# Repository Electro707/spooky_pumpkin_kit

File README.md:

# Scary Pumpkin Soldering Kit with Touch
## Designed by Electro707

This soldering kit is for a pumpkin in which you can touch the nose area to change the LED's effects,
or put the pumpkin in sleep mode until the next Halloween season!

## Credit
The outline for the board, as mention in the [Outline_Graphics](Outline_Graphics) folder, are a combination of some vector graphics from Wikimedia, which are
- [Pumpkinn.svg](https://commons.wikimedia.org/wiki/File:Pumpkinn.svg), under the [CC0 1.0 Universal Public Domain Dedication](https://creativecommons.org/publicdomain/zero/1.0/deed.en) license.
- [Scary_pumpkin_3.svg](https://commons.wikimedia.org/wiki/File:Scary_pumpkin_3.svg), under the [GNU Free Documentation License](https://commons.wikimedia.org/wiki/Commons:GNU_Free_Documentation_License,_version_1.2)

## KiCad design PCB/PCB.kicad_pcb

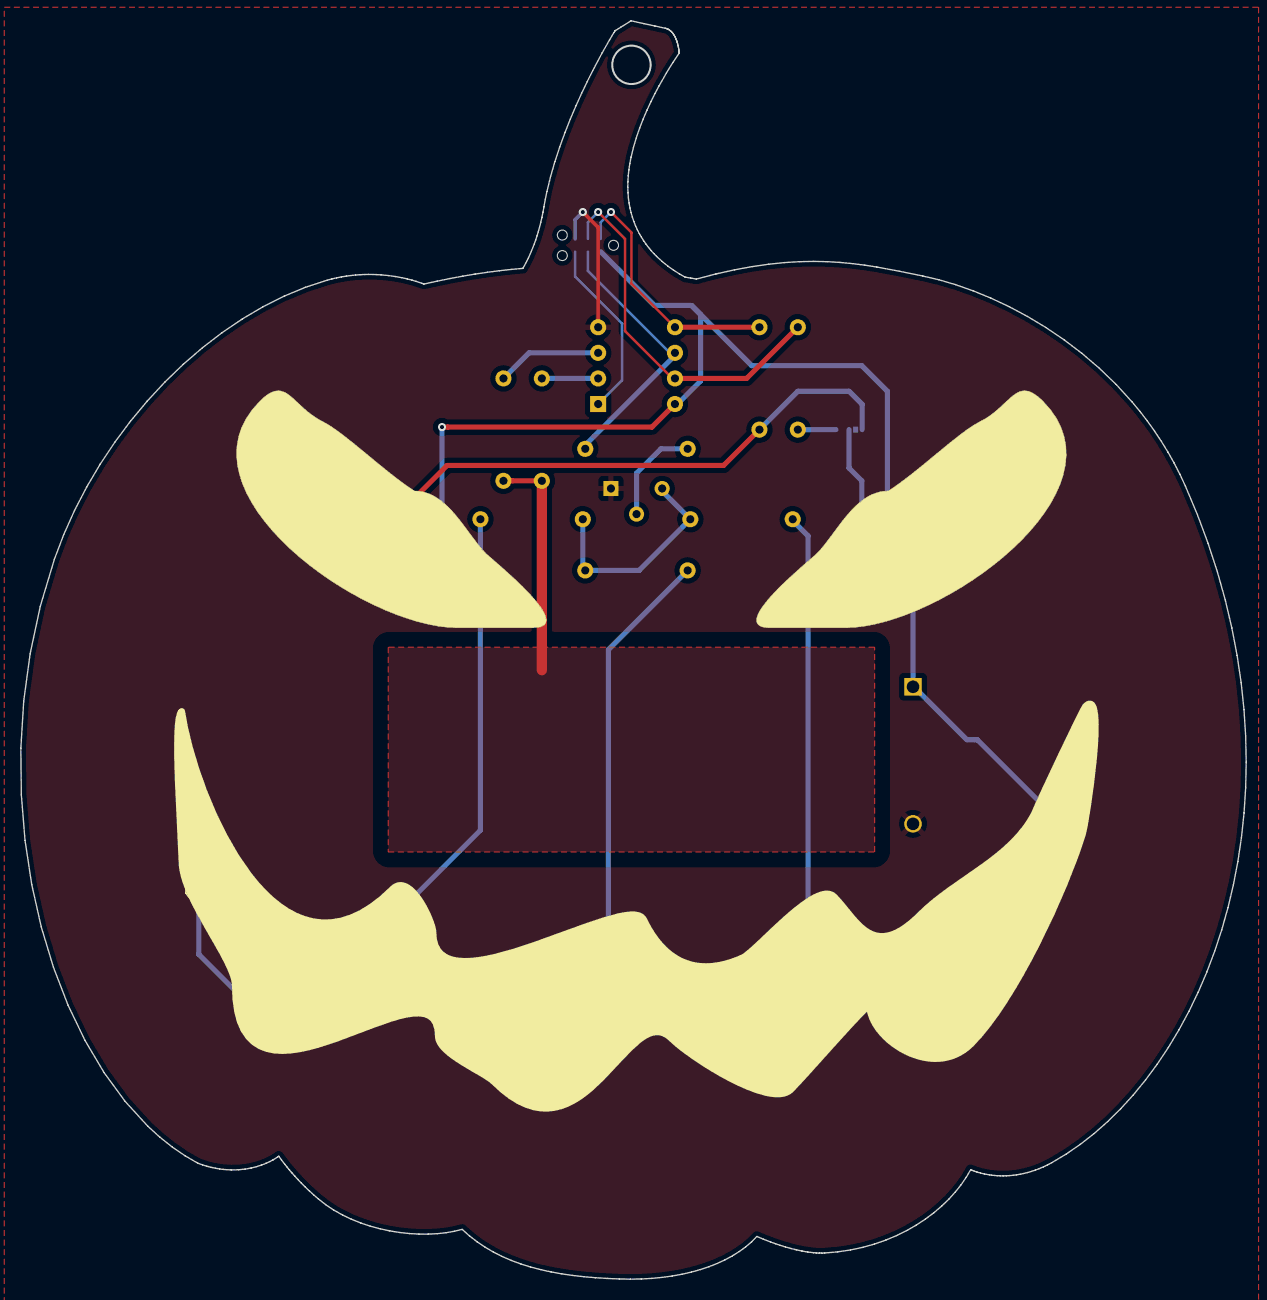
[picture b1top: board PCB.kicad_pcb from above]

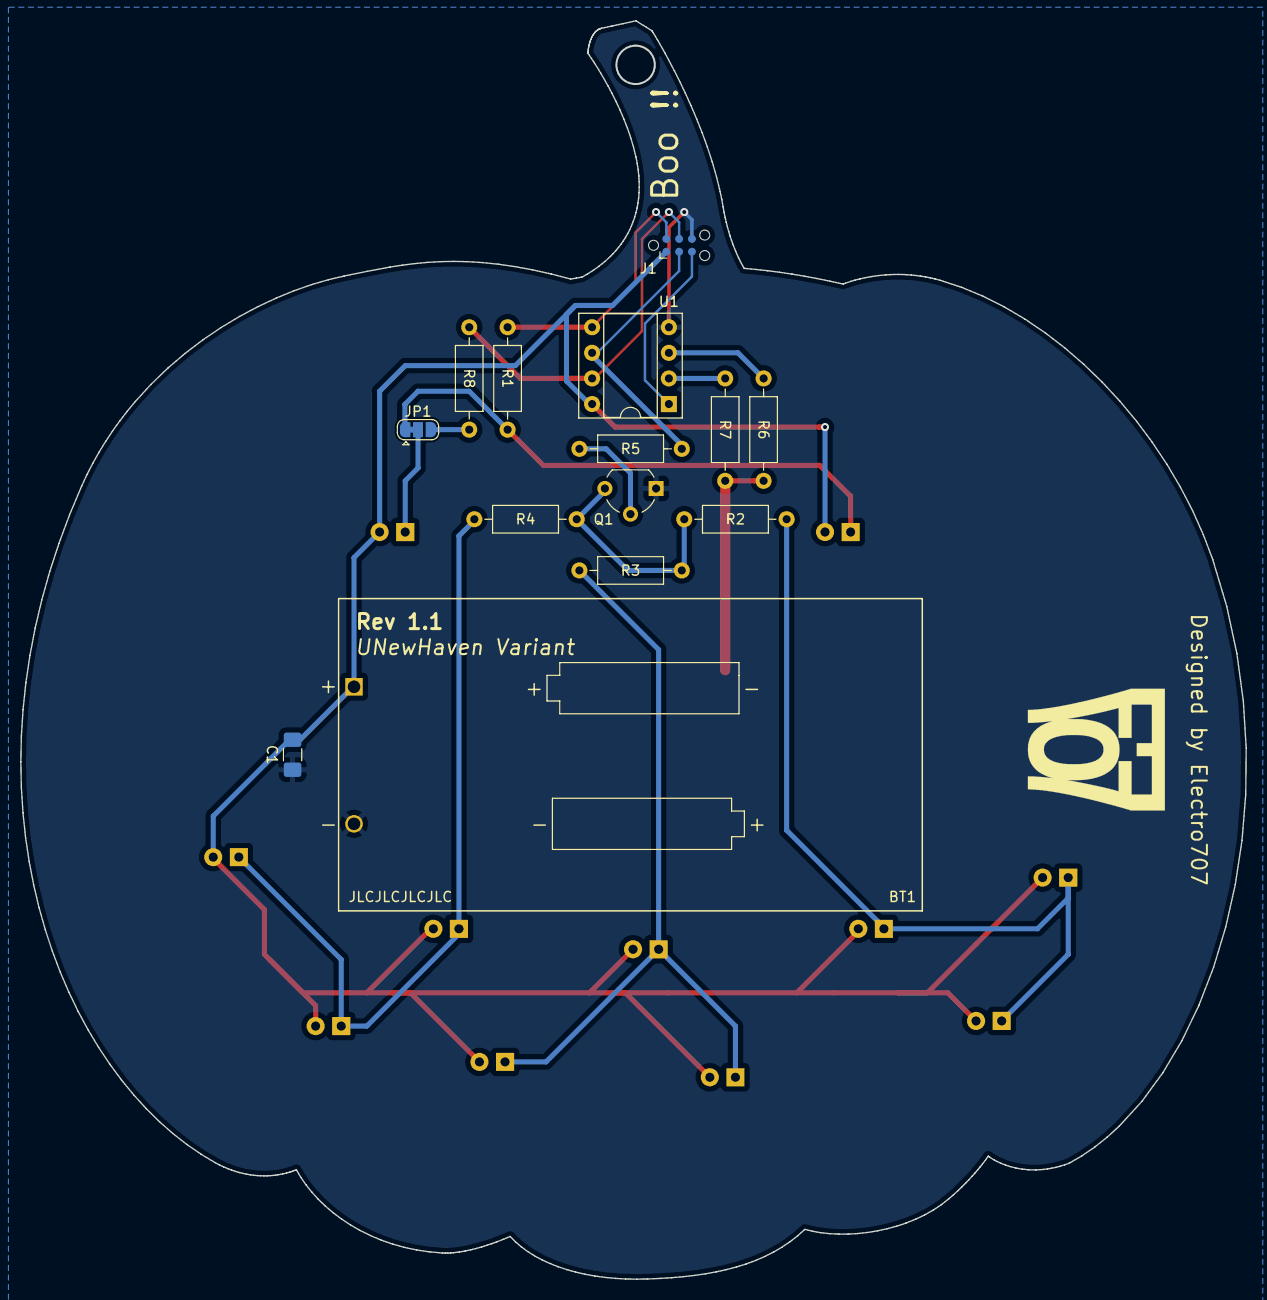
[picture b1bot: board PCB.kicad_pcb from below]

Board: 2 copper layers, 121.6 x 124.9 mm, 25 parts (14 on the bottom side), 17 nets.

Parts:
BT1: Battery; BC2AAPC
C1: 1uF; C_1206_3216Metric_Pad1.42x1.75mm_HandSolder
D1, D2, D3, D4, D5, D6, D7, D8, D9, D10, D11: LED_ALT; LED_D5.0mm
J1: Conn_01x06; Tag-Connect_TC2030-IDC-NL_2x03_P1.27mm_Vertical
JP1: SolderJumper_3_Bridged12; SolderJumper-3_P1.3mm_Bridged12_RoundedPad1.0x1.5mm
Q1: 2N3904; TO-92_Wide
R1, R2, R3, R4, R8: 330; R_Axial_DIN0207_L6.3mm_D2.5mm_P10.16mm_Horizontal
R5, R7: 1k; R_Axial_DIN0207_L6.3mm_D2.5mm_P10.16mm_Horizontal
R6: 1M; R_Axial_DIN0207_L6.3mm_D2.5mm_P10.16mm_Horizontal
U1: ATtiny85-20PU; DIP-8_W7.62mm_Socket

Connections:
CopperPad: R6.2, R7.2
GND: BT1.2 (-), C1.2, J1.6, Q1.1 (E), U1.4 (GND)
unnamed: D1.1 (K), JP1.1 (A), R1.1
unnamed: D2.1 (K), JP1.2 (C)
unnamed: D3.1 (K), D4.1 (K), D5.1 (K), R2.1
unnamed: J1.2, R1.2, U1.5 (AREF/PB0)
unnamed: J1.3, R5.2, U1.6 (PB1)
unnamed: J1.4, R8.2, U1.7 (PB2)
unnamed: J1.5, U1.1 (~RESET/PB5)
unnamed: JP1.3 (B), R8.1
unnamed: Q1.2 (B), R5.1
unnamed: Q1.3 (C), R2.2, R3.2, R4.2
unnamed: D6.1 (K), D7.1 (K), D8.1 (K), R3.1
unnamed: D9.1 (K), D10.1 (K), D11.1 (K), R4.1
unnamed: R7.1, U1.2 (XTAL1/PB3)
unnamed: R6.1, U1.3 (XTAL2/PB4)
VCC: BT1.1 (+), C1.1, D1.2 (A), D2.2 (A), D3.2 (A), D4.2 (A), D5.2 (A), D6.2 (A), D7.2 (A), D8.2 (A), D9.2 (A), D10.2 (A), D11.2 (A), J1.1, U1.8 (VCC)

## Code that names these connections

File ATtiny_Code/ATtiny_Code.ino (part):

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#include <CapacitiveSensor.h>     // Import the library
#include <avr/sleep.h>
#include<avr/wdt.h>
#define EYE_LED_PIN PB0           // Define the eye control LED pin
#define EYE_LEFT_LEN_PIN PB2      // Define the other eye control light if the jumper is cut away
#define MOUTH_LED_PIN PB1         // Define the LED pin
#define CAPSENSE_SEND PB4         // Define the capacitive touch send pin
#define CAPSENSE_REC  PB3         // Define the capacitive touch recieve pin

typedef uint8_t flag;

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
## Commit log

2022-12-05 Changed default version to remove UNH logo
